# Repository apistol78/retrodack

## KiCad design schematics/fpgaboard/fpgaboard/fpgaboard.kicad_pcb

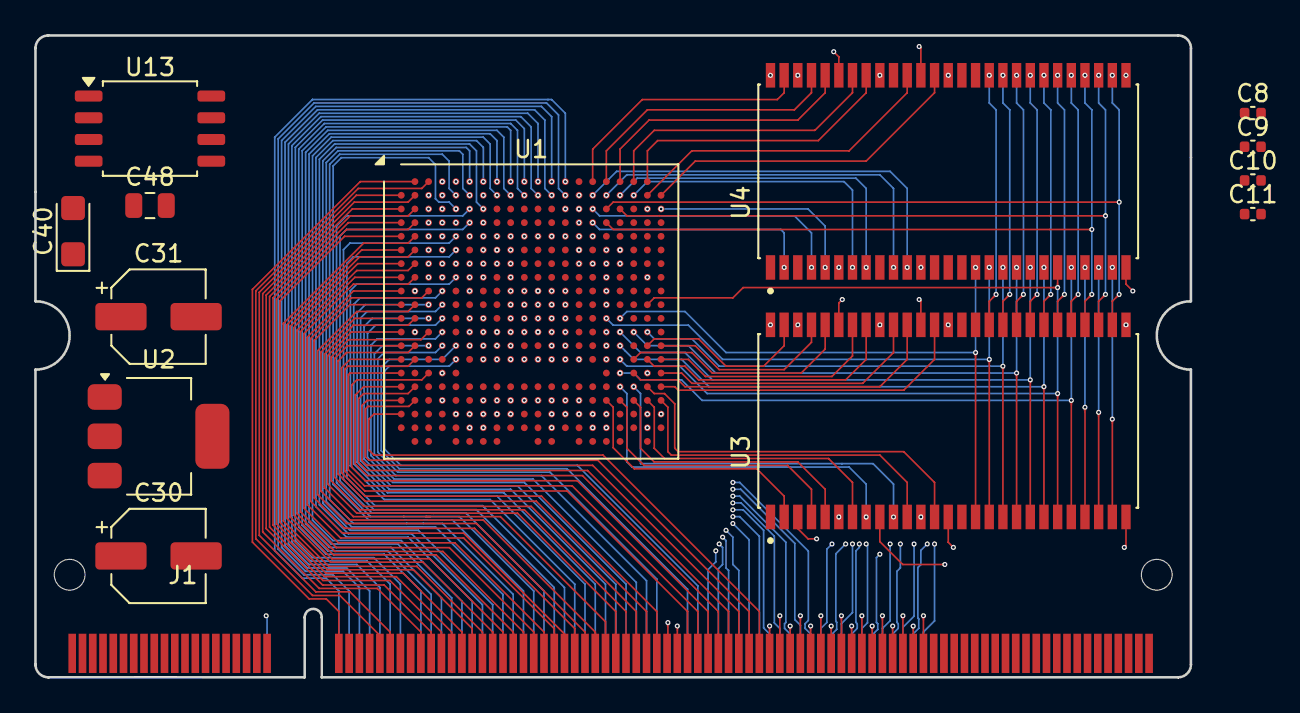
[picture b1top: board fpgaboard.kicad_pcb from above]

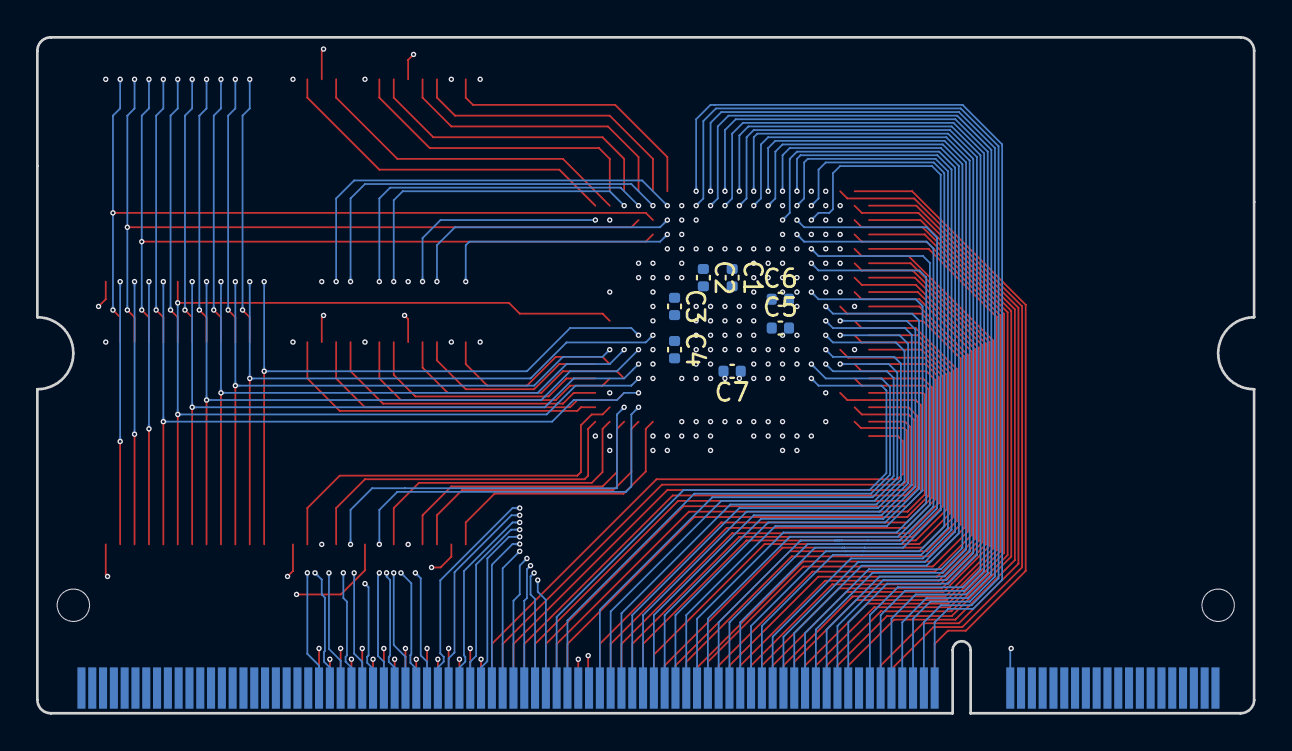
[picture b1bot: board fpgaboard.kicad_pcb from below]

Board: 6 copper layers, 67.6 x 37.5 mm, 21 parts (7 on the bottom side), 171 nets.

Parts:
C1, C2, C3, C4, C5, C6, C7, C8, C9, C10, C11: C_Small; C_0402_1005Metric
C30: 10uF; CP_Elec_5x5.3
C31: 22uF; CP_Elec_5x5.3
C40: 47uF; CP_EIA-3216-18_Kemet-A
C48: 1uF; C_0805_2012Metric
J1: SODIMM-200; SODIMM_DDR2_EDGE
U1: LFE5UM-85F-8BG381I; Lattice_caBGA-381_17x17mm_Layout20x20_P0.8mm
U2: AMS1117-3.3; SOT-223-3_TabPin2
U3, U4: IS42S16320F-7TL; SOP80P1176X120-54N
U13: W25Q32JVSS; SOIC-8_5.3x5.3mm_P1.27mm

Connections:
1v1: U1.H8 (VCC), U1.H9 (VCC), U1.H10 (VCC), U1.H11 (VCC), U1.H12 (VCC), U1.H13 (VCC), U1.J8 (VCC), U1.J13 (VCC), U1.K8 (VCC), U1.K13 (VCC), U1.L8 (VCC), U1.L13 (VCC), U1.M8 (VCC), U1.M13 (VCC), U1.N8 (VCC), U1.N9 (VCC), U1.N10 (VCC), U1.N11 (VCC), U1.N12 (VCC), U1.N13 (VCC)
5V0: C30.1, J1.2, J1.4, J1.6, J1.8, J1.10, J1.12, U2.3 (VI)
FLASH_CLK: U1.U3 (CCLK), U13.6 (CLK)
FLASH_CSn: U1.R2 (PB15A), U13.1 (~CS)
FLASH_IO0: U1.W2 (PB11B), U13.5 (DI/IO_{0})
FLASH_IO1: U1.V2 (PB11A), U13.2 (DO/IO_{1})
FLASH_IO2: U1.Y2 (PB9B), U13.3 (~WP/IO_{2})
FLASH_IO3: U1.W1 (PB9A), U13.7 (~HOLD/~RESET/IO_{3})
GND: C1.2, C2.2, C3.2, C4.2, C5.2, C6.2, C7.2, C8.2, C9.2, C10.2, C11.2, C30.2, C31.2, C40.2, C48.1, J1.1, J1.3, J1.5, J1.7, J1.9, J1.11, J1.39, J1.40, J1.55, J1.56, J1.105, J1.106, J1.107, J1.108, J1.157, J1.158, J1.199, J1.200, U1.B7 (GND), U1.B14 (GND), U1.C19 (GND), U1.D4 (GND), U1.F7 (GND), U1.F8 (GND), U1.F13 (GND), U1.F14 (GND), U1.G4 (GND), U1.G6 (GND), U1.G7 (GND), U1.G8 (GND), U1.G9 (GND), U1.G10 (GND), U1.G11 (GND), U1.G12 (GND), U1.G13 (GND), U1.G14 (GND), U1.G15 (GND), U1.G17 (GND), U1.H19 (GND), U1.J2 (GND), U1.J7 (GND), U1.J9 (GND), U1.J10 (GND), U1.J11 (GND), U1.J12 (GND), U1.J14 (GND), U1.K6 (GND), U1.K7 (GND), U1.K9 (GND), U1.K10 (GND), U1.K11 (GND), U1.K12 (GND), U1.K14 (GND), U1.K15 (GND), U1.L9 (GND), U1.L10 (GND), U1.L11 (GND), U1.L12 (GND), U1.M2 (GND), U1.M7 (GND), U1.M9 (GND), U1.M10 (GND), U1.M11 (GND), U1.M12 (GND), U1.M14 (GND), U1.M16 (GND), U1.N6 (GND), U1.N7 (GND), U1.N14 (GND), U1.N15 (GND), U1.P7 (GND), U1.P8 (GND), U1.P11 (GND), U1.P12 (GND), U1.P13 (GND), U1.P14 (GND), U1.R4 (CFG_2), U1.R19 (GND), U1.U4 (CFG_0), U1.U7 (GND), U1.U8 (GND), U1.U9 (GND), U1.U10 (GND), U1.U11 (GND), U1.U12 (GND), U1.U13 (GND), U1.U14 (GND), U1.V5 (GND), U1.V6 (GND), U1.V7 (GND), U1.V8 (GND), U1.V9 (GND), U1.V12 (GND), U1.V13 (GND), U1.V14 (GND), U1.V15 (GND), U1.V16 (GND), U1.V19 (GND), U1.V20 (GND), U1.W6 (GND), U1.W7 (GND), U1.W12 (GND), U1.W15 (GND), U1.W16 (GND), U1.W19 (GND), U2.1 (GND), U3.6 (VSSQ), U3.12 (VSSQ), U3.28 (VSS), U3.41 (VSS), U3.46 (VSSQ), U3.52 (VSSQ), U3.54 (VSS), U4.6 (VSSQ), U4.12 (VSSQ), U4.28 (VSS), U4.41 (VSS), U4.46 (VSSQ), U4.52 (VSSQ), U4.54 (VSS), U13.4 (GND)
IO_3v3: C1.1, C2.1, C3.1, C4.1, C5.1, C6.1, C7.1, C8.1, C9.1, C10.1, C11.1, C31.1, C40.1, C48.2, U1.F9 (VCCIO0), U1.F10 (VCCIO0), U1.F11 (VCCIO1), U1.F12 (VCCIO1), U1.H6 (VCCIO7), U1.H7 (VCCIO7), U1.H14 (VCCIO2), U1.H15 (VCCIO2), U1.J6 (VCCIO7), U1.J15 (VCCIO2), U1.L6 (VCCIO6), U1.L7 (VCCIO6), U1.L14 (VCCIO3), U1.L15 (VCCIO3), U1.M6 (VCCIO6), U1.M15 (VCCIO3), U1.P9 (VCCIO8), U1.P10 (VCCIO8), U2.2 (VO), U3.1 (VDD), U3.3 (VDDQ), U3.9 (VDDQ), U3.14 (VDD), U3.27 (VDD), U3.43 (VDDQ), U3.49 (VDDQ), U4.1 (VDD), U4.3 (VDDQ), U4.9 (VDDQ), U4.14 (VDD), U4.27 (VDD), U4.43 (VDDQ), U4.49 (VDDQ), U13.8 (VCC)
unnamed: U1.T6 (VCCA0), U1.U6 (VCCA0)
unnamed: U1.T15 (VCCA1), U1.U15 (VCCA1)
unnamed: U1.F6 (VCCAUX), U1.F15 (VCCAUX), U1.P6 (VCCAUX), U1.P15 (VCCAUX)
unnamed: U1.V10 (VCCAUXA0), U1.V11 (VCCAUXA0)
unnamed: U1.V17 (VCCAUXA1), U1.V18 (VCCAUXA1)
RAM_A0: U1.R17 (PR56D), U3.23 (A0), U4.23 (A0)
RAM_A1: U1.E20 (PR38A), U3.24 (A1), U4.24 (A1)
RAM_A2: U1.F19 (PR38B), U3.25 (A2), U4.25 (A2)
RAM_A3: U1.F20 (PR38C), U3.26 (A3), U4.26 (A3)
RAM_A4: U1.C16 (PT112A), U1.G20 (PR38D), U3.29 (A4), U4.29 (A4)
RAM_A5: U1.C17 (PT114B), U1.G19 (PR41A), U3.30 (A5), U4.30 (A5)
RAM_A6: U1.D16 (PT112B), U1.H20 (PR41B), U3.31 (A6), U4.31 (A6)
RAM_A7: U1.J18 (PR41C), U3.32 (A7), U4.32 (A7)
RAM_A8: U1.K18 (PR41D), U3.33 (A8), U4.33 (A8)
RAM_A9: U1.J19 (PR44A), U3.34 (A9), U4.34 (A9)
RAM_A10: U1.P17 (PR53D), U3.22 (A10), U4.22 (A10)
RAM_A11: U1.J20 (PR44C), U3.35 (A11), U4.35 (A11)
RAM_A12: U1.K20 (PR44D), U3.36 (A12), U4.36 (A12)
RAM_BA0: U1.M17 (PR53B), U3.20 (BA0), U4.20 (BA0)
RAM_BA1: U1.N17 (PR56A), U3.21 (BA1), U4.21 (BA1)
RAM_CKE: U1.M20 (PR47B), U3.37 (CKE), U4.37 (CKE)
RAM_CLK: U1.L20 (PR47A), U3.38 (CLK), U4.38 (CLK)
RAM_D0: U1.U16 (PR92C), U3.2 (DQ0)
RAM_D1: U1.U17 (PR92B), U3.4 (DQ1)
RAM_D2: U1.U18 (PR92A), U3.5 (DQ2)
RAM_D3: U1.U19 (PR89C), U3.7 (DQ3)
RAM_D4: U1.T17 (PR92D), U3.8 (DQ4)
RAM_D5: U1.T18 (PR89D), U3.10 (DQ5)
RAM_D6: U1.U20 (PR86D), U3.11 (DQ6)
RAM_D7: U1.T19 (PR89A), U3.13 (DQ7)
RAM_D8: U1.T20 (PR86C), U3.42 (DQ8)
RAM_D9: U1.R18 (PR89B), U3.44 (DQ9)
RAM_D10: U1.R20 (PR86B), U3.45 (DQ10)
RAM_D11: U1.P19 (PR83C), U3.47 (DQ11)
RAM_D12: U1.P20 (PR86A), U3.48 (DQ12)
RAM_D13: U1.P18 (PR83D), U3.50 (DQ13)
RAM_D14: U1.N20 (PR83B), U3.51 (DQ14)
RAM_D15: U1.N19 (PR83A), U3.53 (DQ15)
RAM_D16: U1.D15 (PT107A), U4.2 (DQ0)
RAM_D17: U1.C15 (PT105B), U4.4 (DQ1)
RAM_D18: U1.C20 (PR35A), U4.5 (DQ2)
RAM_D19: U1.B18 (PT116B), U4.7 (DQ3)
RAM_D20: U1.B17 (PT114A), U4.8 (DQ4)
RAM_D21: U1.B16 (PT110B), U4.10 (DQ5)
RAM_D22: U1.B15 (PT105A), U4.11 (DQ6)
RAM_D24: U1.B20 (PT121B), U4.42 (DQ8)
RAM_D27: U1.A19 (PT121A), U4.47 (DQ11)
RAM_D28: U1.A18 (PT119A), U4.48 (DQ12)
RAM_D29: U1.A17 (PT116A), U4.50 (DQ13)
RAM_D30: U1.A16 (PT110A), U4.51 (DQ14)
RAM_D31: U1.A15 (PT103A), U4.53 (DQ15)
S1: J1.41, U1.A2 (PL35A)
S2: J1.49, U1.A3 (PL14C)
S3: J1.51, U1.B1 (PL35B)
S4: J1.57, U1.B2 (PL35C)
S5: J1.59, U1.C1 (PL38A)
S6: J1.61, U1.C2 (PL35D)
S7: J1.63, U1.D1 (PL38B)
S8: J1.65, U1.D2 (PL38C)
S9: J1.67, U1.E1 (PL38D)
S10: J1.69, U1.E2 (PL44D)
S11: J1.71, U1.F1 (PL47B)
S12: J1.73, U1.F2 (PL44C)
S13: J1.75, U1.G1 (PL47D)
S14: J1.77, U1.G2 (PL47A)
S15: J1.79, U1.H1 (PL53C)
S16: J1.81, U1.H2 (PL47C)
S17: J1.83, U1.J1 (PL53B)
S18: J1.85, U1.J3 (PL50C)
S19: J1.87, U1.K1 (PL53D)
S20: J1.89, U1.K2 (PL53A)
S21: J1.91, U1.L1 (PL89C)
S22: J1.93, U1.L2 (PL86D)
S23: J1.95, U1.M1 (PL89B)
S24: J1.97, U1.M3 (PL86B)
S25: J1.99, U1.N1 (PL89D)
S26: J1.101, U1.N2 (PL89A)
S27: J1.103, U1.P1 (PL92A)
S28: J1.109, U1.P2 (PL92B)
S29: J1.111, U1.R1 (PB4A)
S30: J1.113, U1.R3 (PB15B)
S31: J1.115, U1.T1 (PB4B)
S32: J1.117, U1.T2 (PB13A)
S33: J1.119, U1.U1 (PB6A)
S34: J1.121, U1.U2 (PB13B)
S35: J1.123, U1.V1 (PB6B)
S36: J1.125, U1.A4 (PL11A)
S37: J1.127, U1.A5 (PL11B)
S38: J1.129, U1.B3 (PL14D)
S39: J1.131, U1.B4 (PL14B)
S40: J1.133, U1.C3 (PL17C)
S41: J1.135, U1.C4 (PL14A)
S42: J1.137, U1.D3 (PL17D)
S43: J1.139, U1.D5 (PL17B)
S44: J1.141, U1.E3 (PL20B)
S45: J1.143, U1.E4 (PL17A)
S46: J1.145, U1.F3 (PL44B)
S47: J1.147, U1.F4 (PL20A)
S48: J1.149, U1.G3 (PL44A)
S49: J1.151, U1.G5 (PL41B)
S50: J1.153, U1.H3 (PL41D)
S51: J1.155, U1.H4 (PL41A)
S52: J1.42, U1.A13 (PT76B)
S53: J1.44, U1.B13 (PT78A)
S54: J1.46, U1.A12 (PT76A)
S55: J1.48, U1.B12 (PT71A)
S56: J1.50, U1.A11 (PT63B)
S57: J1.52, U1.B11 (PT65A)
S58: J1.54, U1.A10 (PT63A)
S59: J1.58, U1.B10 (PT60B)
S60: J1.60, U1.A9 (PT60A)
S61: J1.62, U1.B9 (PT58A)
S62: J1.64, U1.A8 (PT18B)
S63: J1.66, U1.B8 (PT15B)
S64: J1.68, U1.A7 (PT18A)
S65: J1.70, U1.C7 (PT11B)
S66: J1.72, U1.A6 (PT4A)
S67: J1.74, U1.B6 (PT4B)
S68: J1.76, U1.B5 (PL11C)
S69: J1.78, U1.C5 (PL11D)
S70: J1.80, U1.C6 (PT11A)
S71: J1.82, U1.D6 (PT6B)
S72: J1.84, U1.E5 (PL20C)
S73: J1.86, U1.F5 (PL20D)
S74: J1.88, U1.H5 (PL41C)
S75: J1.90, U1.J4 (PL50A)
S76: J1.92, U1.K3 (PL50D)
S77: J1.94, U1.K4 (PL56A)
S78: J1.96, U1.L3 (PL86C)
S79: J1.98, U1.L4 (PL56C)
S80: J1.100, U1.M4 (PL83A)
S81: J1.102, U1.N3 (PL86A)
S82: J1.104, U1.N4 (PL83C)
S83: J1.110, U1.N5 (PL83B)
S84: J1.112, U1.P5 (PL83D)
S85: J1.114, U1.E6 (PT6A)
S86: J1.116, U1.D7 (PT9B)
S87: J1.118, U1.E7 (PT9A)
S88: J1.120, U1.E8 (PT13A)
S89: J1.122, U1.E9 (PT20B)
S90: J1.124, U1.E10 (PT56B)
S91: J1.126, U1.E11 (PT69B)
S92: J1.128, U1.E12 (PT74B)
S93: J1.130, U1.E13 (PT80B)
S94: J1.132, U1.E14 (PT85B)
S95: J1.134, U1.F16 (PR11D)
S96: J1.136, U1.P16 (PR56B)
S97: J1.138, U1.N16 (PR53A)
S98: J1.140, U1.K16 (PR29A)
S99: J1.142, U1.J16 (PR20D)
S100: J1.144, U1.H16 (PR17D)
S101: J1.146, U1.G16 (PR17C)
S102: J1.148, U1.F17 (PR17A)
S103: J1.150, U1.E15 (PT107B)
S104: J1.152, U1.D14 (PT85A)
S105: J1.154, U1.C13 (PT78B)
S106: J1.156, U1.C14 (PT83B)
~RAM_CAS: U1.L16 (PR50A), U3.17 (~CAS), U4.17 (~CAS)
~RAM_CS: U1.M18 (PR50D), U3.19 (~CS), U4.19 (~CS)
~RAM_RAS: U1.M19 (PR47D), U3.18 (~RAS), U4.18 (~RAS)
~RAM_WE: U1.L17 (PR50B), U3.16 (~WE), U4.16 (~WE)

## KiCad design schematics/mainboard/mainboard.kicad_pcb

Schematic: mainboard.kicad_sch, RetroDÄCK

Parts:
C1, C17, C27, C30: 10uF; CP_Elec_5x5.3
C2, C31: 22uF; CP_Elec_5x5.3
C3, C4, C5, C6, C7, C8, C10, C11, C12, C13, C14, C48, C49: 1uF; C_0805_2012Metric
C9: 4.7uF; C_0805_2012Metric
C15, C21, C23, C26, C32, C35, C36: 0.1uF; C_0805_2012Metric_Pad1.18x1.45mm_HandSolder; LCSC C28233
C16, C28, C29: 10uF; C_0805_2012Metric
C18: 0.1uF; C_0805_2012Metric
C19, C20: 27pF; C_0805_2012Metric
C22, C24, C33, C37: 10uF; C_0805_2012Metric_Pad1.18x1.45mm_HandSolder; LCSC C1713
C25, C40, C43, C45: 47uF; CP_EIA-3216-18_Kemet-A; LCSC C7190
C34, C38: 22uF; C_0805_2012Metric_Pad1.18x1.45mm_HandSolder; LCSC C15850
C39: 47uF; CP_Elec_5x5.3
C41: 500pF; C_0805_2012Metric
C42: 10uF; CP_EIA-3216-18_Kemet-A; LCSC C1969735
C44: 0.47uF; C_0805_2012Metric_Pad1.18x1.45mm_HandSolder
C46, C47: 47uF; C_0805_2012Metric_Pad1.18x1.45mm_HandSolder
D1, D3: LED; LED_0805_2012Metric; LCSC C2297
H1, H2, H3, H4, H5, H6, H7, H8: MountingHole; MountingHole_2.5mm
J1: SD_Card_Receptacle; RetroDACK SD_Hirose_DM1AA_SF_PEJ82; LCSC C506790
J2: LCD_CONN; PinHeader_2x20_P2.54mm_Vertical
J3: USB_C_Receptacle_USB2.0_16P; USB_C_Receptacle_GCT_USB4105-xx-A_16P_TopMnt_Horizontal
J4: BATTERY_CONN; JST_PH_S2B-PH-K_1x02_P2.00mm_Horizontal
J5: 527461671; CON_527461671_MOL; LCSC C3169781
J6: SPEAKER_CONN; JST_PH_S2B-PH-K_1x02_P2.00mm_Horizontal
J7: Conn_01x06; PinHeader_1x06_P2.54mm_Vertical
L1: 2.2uH; L_APV_ANR4012; LCSC C36409
P1: 1-1473005-4; TE_1-1473005-4; LCSC C428482
R1, R2: 33; R_0603_1608Metric_Pad0.98x0.95mm_HandSolder
R3, R4: 1.2k; R_0603_1608Metric_Pad0.98x0.95mm_HandSolder
R5: 100; R_0603_1608Metric
R6, R7: 5.1k; R_0603_1608Metric_Pad0.98x0.95mm_HandSolder
R8, R9, R10, R11, R12, R13, R14, R15, R16, R18, R19, R20, R28, R31, R35, R36: 10k; R_0603_1608Metric_Pad0.98x0.95mm_HandSolder
R17, R33, R34: 4k7; R_0603_1608Metric_Pad0.98x0.95mm_HandSolder; LCSC C17673
R21, R22, R23, R24, R25: 4k7; R_0603_1608Metric_Pad0.98x0.95mm_HandSolder
R26: 120; R_0603_1608Metric_Pad0.98x0.95mm_HandSolder
R27: 68; R_0603_1608Metric_Pad0.98x0.95mm_HandSolder
R29: 0; R_0805_2012Metric_Pad1.20x1.40mm_HandSolder
R30: 10m (1%, 1W); R_0805_2012Metric
R32: NC; R_0603_1608Metric_Pad0.98x0.95mm_HandSolder
S1: SSSS811101; SW_SSSS811101; PARTREV N/A
U1, U2: AMS1117-3.3; SOT-223-3_TabPin2
U3: MAX3421EETJ_T; QFP50P700X700X120-32N; LCSC C2651881
U4: SOP80P1176X120-54N; LCSC C2959389
U5: AMS1117-1.8; SOT-223-3_TabPin2; LCSC C6185
U6: TPS63002; Texas_DRC0010J_ThermalVias; LCSC C116655
U7: BQ24072RGT; VQFN-16-1EP_3x3mm_P0.5mm_EP1.6x1.6mm; LCSC C81080
U8: QFN50P500X500X100-33N; LCSC C2667049
U9: TPS22917DBV; SOT-23-6; LCSC C2681320
U10: PCA9555PW; TSSOP-24_4.4x7.8mm_P0.65mm; LCSC C128392
U11: PJ-327E-5A; LCSC C145812
U13: W25Q32JVSS; SOIC-8_5.3x5.3mm_P1.27mm; LCSC C82344
U14: DS3231MZ; SOIC-8_3.9x4.9mm_P1.27mm; LCSC C107410
U15: BQ27441DRZT-G1A; Texas_S-PDSO-N12; LCSC C2864880
Y1: 12MHz; Crystal_SMD_HC49-SD

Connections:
1V8: C21.1, C22.1, C25.1, U5.2 (VO), U8.3 (DVDD)
3V3: C6.1, C7.1, C8.2, C10.2, C11.2, C12.2, C13.2, C14.2, C23.1, C24.1, C26.1, C31.1, C33.1, C35.1, C37.1, C40.1, C42.1, C49.2, J5.15, R8.2, R9.2, R10.2, R11.2, R12.2, R13.2, R14.2, R15.2, R16.2, R17.1, R18.2, R20.2, R33.1, R34.1, R36.2, U2.2 (VO), U3.2 (VL), U3.23 (VCC), U4.2 (VCC), U4.14 (VCC), U4.16 (~CE2), U4.23 (VCC), U4.29 (VCC), U4.50 (VCC), U5.3 (VI), U8.2 (IOVDD), U8.17 (AVDD), U8.28 (HPVDD), U10.24 (VDD), U14.2 (VCC)
3V3_LCD: C2.1, C3.2, C4.2, C39.1, C43.1, C48.2, J1.4 (VDD), J1.14 (CARD_DETECT), J2.1, J2.17, R21.2, R22.2, R23.2, R24.2, R25.2, U1.2 (VO), U13.8 (VCC)
5V0: C1.1, C16.2, C29.2, C30.1, C32.1, C34.1, C36.1, C38.1, C45.1, J2.2, J2.4, P1.2, P1.4, P1.6, P1.8, P1.10, P1.12, U1.3 (VI), U2.3 (VI), U6.1 (VOUT), U6.10 (FB), U8.21 (SPKVDD), U8.24 (SPKVDD)
AUDIO_BCLK: P1.66, U8.7 (BCLK)
AUDIO_DIN: P1.70, U8.5 (DIN)
AUDIO_INTERRUPT: P1.72, U8.32 (GPIO1)
AUDIO_MCLK: P1.64, U8.8 (MCLK)
AUDIO_WCLK: P1.68, U8.6 (WCLK)
BAT+: J4.1, R30.2, U15.6 (BAT), U15.8 (SRP)
BAT_SYS+: C9.2, R30.1, U7.2 (BAT), U7.3 (BAT), U14.6 (VBAT), U15.7 (SRN)
FLASH_CLK: P1.92, U13.6 (CLK)
FLASH_CSn: P1.84, U13.1 (~CS)
FLASH_IO0: P1.90, U13.5 (DI/IO_{0})
FLASH_IO1: P1.86, U13.2 (DO/IO_{1})
FLASH_IO2: P1.88, U13.3 (~WP/IO_{2})
FLASH_IO3: P1.94, U13.7 (~HOLD/~RESET/IO_{3})
GND: C1.2, C2.2, C3.1, C4.1, C5.1, C6.2, C7.2, C8.1, C9.1, C10.1, C11.1, C12.1, C13.1, C14.1, C15.2, C16.1, C17.2, C18.1, C19.1, C20.1, C21.2, C22.2, C23.2, C24.2, C25.2, C26.2, C27.2, C28.1, C29.1, C30.2, C31.2, C32.2, C33.2, C34.2, C35.2, C36.2, C37.2, C38.2, C39.2, C40.2, C42.2, C43.2, C44.2, C45.2, C48.1, C49.1, J1.3 (VSS), J1.6 (VSS), J1.12 (SHELL1), J1.13 (SHELL2), J2.6, J2.9, J2.14, J2.20, J2.25, J2.30, J2.34, J2.39, J3.A1 (GND), J3.A12 (GND), J3.B1 (GND), J3.B12 (GND), J3.S1 (SHIELD), J4.2, J5.1, J5.P1, J5.P2, J7.1, P1.1, P1.3, P1.5, P1.7, P1.9, P1.11, P1.39, P1.40, P1.55, P1.56, P1.105, P1.106, P1.107, P1.108, P1.157, P1.158, P1.199, P1.200, R3.2, R4.2, R6.1, R7.1, R19.2, R28.2, R35.2, U1.1 (GND), U2.1 (GND), U3.3 (GND), U3.19 (GND), U4.5 (VSS), U4.13 (~CE1), U4.26 (VSS), U4.32 (VSS), U4.41 (VSS), U4.53 (VSS), U5.1 (GND), U6.3 (PGND), U6.9 (GND), U6.11 (PGND), U7.4 (~CE), U7.6 (EN1), U7.8 (VSS), U7.17 (VSS), U8.1 (IOVSS), U8.13 (AIN1), U8.14 (AIN2), U8.16 (AVSS), U8.18 (DVSS), U8.20 (SPKVSS), U8.25 (SPKVSS), U8.29 (HPVSS), U9.2 (GND), U10.2 (A1), U10.3 (A2), U10.12 (VSS), U10.21 (A0), U11.1 (GND), U13.4 (GND), U14.5 (GND), U15.3 (V_{SS})
I2C_SCL: J5.13, P1.60, R34.2, U8.10 (SCL), U10.22 (SCL), U14.8 (SCL), U15.2 (SCL)
I2C_SDA: J5.12, P1.58, R33.2, U8.9 (SDA), U10.23 (SDA), U14.7 (SDA), U15.1 (SDA)
KEYPAD_INTERRUPT: P1.155, R18.1, U10.1 (~INT)
LCD_B0: J2.7, P1.114
LCD_B1: J2.29, P1.142
LCD_B2: J2.31, P1.144
LCD_B3: J2.26, P1.136
LCD_B4: J2.24, P1.134
LCD_B5: J2.21, P1.132
LCD_BACKLIGHT_CTRL: J2.35, P1.152
LCD_CLK: J2.27, P1.138
LCD_CS: J2.12, P1.122
LCD_ENABLE: J2.28, P1.140
LCD_G0: J2.32, P1.146
LCD_G1: J2.33, P1.148
LCD_G2: J2.8, P1.116
LCD_G3: J2.10, P1.118
LCD_G4: J2.36, P1.150
LCD_G5: J2.11, P1.120
LCD_HSYNC: J2.5, P1.112
LCD_R0: J2.38, P1.154
LCD_R1: J2.40, P1.156
LCD_R2: J2.15, P1.126
LCD_R3: J2.16, P1.124
LCD_R4: J2.18, P1.128
LCD_R5: J2.22, P1.130
LCD_VSYNC: J2.3, P1.110
unnamed: D1.2 (A), R27.2
unnamed: D1.1 (K), U7.9 (~CHG)
unnamed: D3.2 (A), R26.2
unnamed: D3.1 (K), U7.7 (~PGOOD)
unnamed: J3.A5 (CC1), R7.2
unnamed: J3.B5 (CC2), R6.2
unnamed: J6.1, U8.22 (SPKP), U8.26 (SPKP)
unnamed: J6.2, U8.19 (SPKM), U8.23 (SPKM)
unnamed: J7.2, P1.82
unnamed: J7.3, P1.80
unnamed: J7.4, P1.78
unnamed: J7.5, P1.76
unnamed: J7.6, P1.74
unnamed: R1.2, U3.21 (D+)
unnamed: R2.2, U3.20 (D-)
unnamed: C5.2, R29.1, U3.22 (VBCOMP)
unnamed: C18.2, R5.1, U6.6 (EN), U6.7 (PS/SYNC), U6.8 (VINA)
unnamed: L1.2, U6.4 (L1)
unnamed: L1.1, U6.2 (L2)
unnamed: C28.2, C41.1, R26.1, R27.1, S1.2, U7.5 (EN2), U7.10 (OUT), U7.11 (OUT), U7.15 (TD), U9.1 (VIN)
unnamed: R3.1, U7.12 (ILIM)
unnamed: R4.1, U7.16 (ISET)
unnamed: R28.1, U7.1 (TS)
unnamed: C47.1, U8.27 (HPL)
unnamed: C46.1, U8.30 (HPR)
unnamed: R31.1, U8.12 (MICBIAS)
unnamed: C41.2, U9.4 (CT)
unnamed: R19.1, S1.1, U9.3 (ON)
unnamed: R32.2, U9.5 (QOD)
unnamed: J5.2, R8.1, U10.4 (IO0_0)
unnamed: J5.3, R12.1, U10.5 (IO0_1)
unnamed: J5.4, R9.1, U10.6 (IO0_2)
unnamed: J5.5, R13.1, U10.7 (IO0_3)
unnamed: J5.6, R10.1, U10.8 (IO0_4)
unnamed: J5.7, R14.1, U10.9 (IO0_5)
unnamed: J5.8, R11.1, U10.10 (IO0_6)
unnamed: J5.9, R15.1, U10.11 (IO0_7)
unnamed: J5.10, R16.1, U10.13 (IO1_0)
unnamed: J5.11, R20.1, U10.14 (IO1_1)
unnamed: R31.2, U8.11 (VOL/MICDET), U11.4 (DETECT_GND)
unnamed: C47.2, U11.2 (LEFT)
unnamed: C46.2, U11.3 (RIGHT)
unnamed: R35.1, U15.10 (BIN)
unnamed: R36.1, U15.12 (GPOUT)
unnamed: C44.1, U15.5 (V_{DD})
SD_CARD: J1.10 (CARD_DETECT), P1.54
SD_CLK: J1.5 (CLK), P1.46
SD_CMD: J1.2 (CMD), P1.48, R25.1
SD_DAT0: J1.7 (DAT0), P1.44, R21.1
SD_DAT1: J1.8 (DAT1), P1.42, R22.1
SD_DAT2: J1.9 (DAT2), P1.52, R23.1
SD_DAT3: J1.1 (CD/DAT3), P1.50, R24.1
SRAM_A0: P1.119, U4.11 (A0)
SRAM_A1: P1.123, U4.10 (A1)
SRAM_A2: P1.127, U4.9 (A2)
SRAM_A3: P1.131, U4.8 (A3)
SRAM_A4: P1.135, U4.7 (A4)
SRAM_A5: P1.133, U4.48 (A5)
SRAM_A6: P1.129, U4.47 (A6)
SRAM_A7: P1.125, U4.46 (A7)
SRAM_A8: P1.121, U4.45 (A8)
SRAM_A9: P1.117, U4.44 (A9)
SRAM_A10: P1.103, U4.38 (A10)
SRAM_A11: P1.99, U4.37 (A11)
SRAM_A12: P1.95, U4.36 (A12)
SRAM_A13: P1.91, U4.35 (A13)
SRAM_A14: P1.87, U4.34 (A14)
SRAM_A15: P1.85, U4.21 (A15)
SRAM_A16: P1.89, U4.20 (A16)
SRAM_A17: P1.93, U4.19 (A17)
SRAM_A18: P1.97, U4.18 (A18)
SRAM_A19: P1.101, U4.17 (A19)
SRAM_D0: P1.81, U4.22 (IO_0)
SRAM_D1: P1.77, U4.24 (IO_1)
SRAM_D2: P1.73, U4.25 (IO_2)
SRAM_D3: P1.69, U4.27 (IO_3)
SRAM_D4: P1.71, U4.28 (IO_4)
SRAM_D5: P1.75, U4.30 (IO_5)
SRAM_D6: P1.79, U4.31 (IO_6)
SRAM_D7: P1.83, U4.33 (IO_7)
SRAM_D8: P1.137, U4.49 (IO_8)
SRAM_D9: P1.141, U4.51 (IO_9)
SRAM_D10: P1.145, U4.52 (IO_10)
SRAM_D11: P1.149, U4.54 (IO_11)
SRAM_D12: P1.151, U4.1 (IO_12)
SRAM_D13: P1.147, U4.3 (IO_13)
SRAM_D14: P1.143, U4.4 (IO_14)
SRAM_D15: P1.139, U4.6 (IO_15)
SYS_LOAD: C17.1, R5.2, R32.1, U6.5 (VIN), U9.6 (VOUT)
TRACKBALL_INTERRUPT: J5.14, P1.62
USB_DN: J3.A7 (D-), J3.B7 (D-), R2.1
USB_DP: J3.A6 (D+), J3.B6 (D+), R1.1
USB_HCI_INT: P1.57, U3.18 (INT)
USB_HCI_MISO: P1.61, U3.15 (MISO)
USB_HCI_MOSI: P1.59, U3.16 (MOSI)
USB_HCI_SCLK: P1.65, U3.13 (SCLK)
USB_HCI_XI: C19.2, U3.24 (XI), Y1.1
USB_HCI_XO: C20.2, U3.25 (XO), Y1.2
USB_VBUS: C27.1, J3.A4 (VBUS), J3.A9 (VBUS), J3.B4 (VBUS), J3.B9 (VBUS), R29.2, U7.13 (IN)
~RESET: C15.1, R17.2, U8.31 (~RESET)
~SRAM_BHE: P1.115, U4.12 (~BHE)
~SRAM_BLE: P1.109, U4.39 (~BLE)
~SRAM_OE: P1.113, U4.42 (~OE)
~SRAM_WE: P1.111, U4.15 (~WE)
~USB_HCI_RESET: P1.67, U3.12 (~RES)
~USB_HCI_SS: P1.63, U3.14 (~SS)

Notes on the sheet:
SRAM
SD CARD
BATTERY MNGR
TLV320 I2C address 0x18
CE2 if U4 is NOT inverted! Symbol incorrect!
I2C address 0x55 (7-bit)
Trackball I2C address 0x0A
REGULATORS
I2C address 0xD0
AUDIO
I2C address 0x40
NV STORAGE
Switch current min 1600 mA
INPUT CONNECTORS
USB INTERFACE
LCD CONNECTOR
RTC
Battery terminal JST-PH
TODO -GPIO with debounce? +Battery ADC -Charge signal to FPGA (open drain?) -What if battery/USB are connected at the same time as "ice" USB? -Power switch, larger? +Headphone detection, MIC/VOLDET need to be pulled down from a R to MIC +Headphone caps on +/- +Improved bulk and filter of 5V

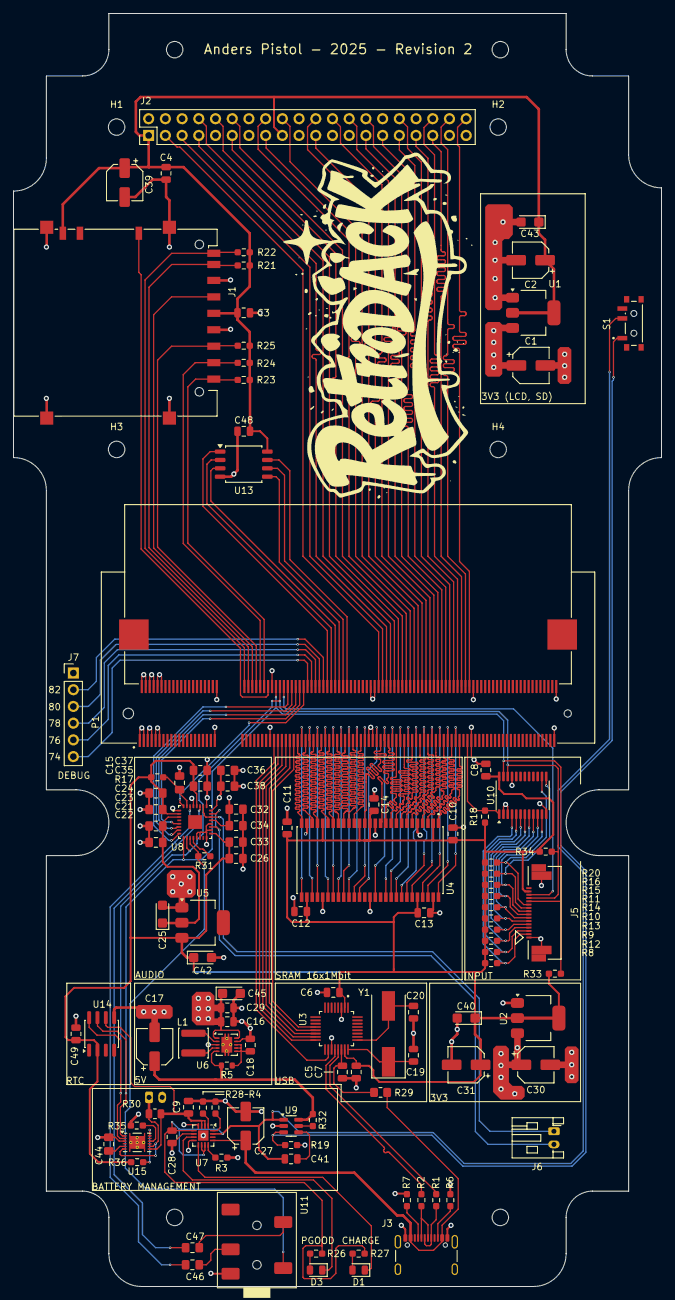
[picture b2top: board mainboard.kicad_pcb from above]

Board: 4 copper layers, 98.5 x 193.5 mm, 120 parts (1 on the bottom side), 151 nets.

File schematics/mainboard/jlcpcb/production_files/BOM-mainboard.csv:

Comment,Designator,Footprint,LCSC,Quantity
0,R29,R_0805_2012Metric_Pad1.20x1.40mm_HandSolder,C17477,1
0.1uF,"C15,C18,C21,C23,C26,C32,C35,C36",C_0805_2012Metric_Pad1.18x1.45mm_HandSolder,C49678,8
0.47uF,C44,C_0805_2012Metric_Pad1.18x1.45mm_HandSolder,C28233,1
1-1473005-4,P1,TE_1-1473005-4,C428482,1
1.2k,"R3,R4",R_0603_1608Metric_Pad0.98x0.95mm_HandSolder,C22765,2
100,R5,R_0603_1608Metric,C22775,1
10k,"R10,R11,R12,R13,R14,R15,R16,R18,R19,R20,R28,R31,R35,R36,R8,R9",R_0603_1608Metric_Pad0.98x0.95mm_HandSolder,C25804,16
"10m (1%, 1W)",R30,R_0805_2012Metric,C728271,1
10uF,"C16,C22,C24,C28,C29,C33,C37",C_0805_2012Metric,C15850,7
10uF,"C1,C17,C27,C30",CP_Elec_5x5.3,C249823,4
10uF,C42,CP_EIA-3216-18_Kemet-A,C74423,1
120,R26,R_0603_1608Metric_Pad0.98x0.95mm_HandSolder,C22787,1
12MHz,Y1,Crystal_SMD_HC49-SD,C521722,1
1uF,"C10,C11,C12,C13,C14,C3,C4,C48,C49,C5,C6,C7,C8",C_0805_2012Metric,C28323,13
2.2uH,L1,L_APV_ANR4012,C36409,1
22uF,"C2,C31",CP_Elec_5x5.3,C249605,2
22uF,"C34,C38",C_0805_2012Metric_Pad1.18x1.45mm_HandSolder,C45783,2
27pF,"C19,C20",C_0805_2012Metric,C1804,2
33,"R1,R2",R_0603_1608Metric_Pad0.98x0.95mm_HandSolder,C23140,2
4.7uF,C9,C_0805_2012Metric,C1779,1
47uF,"C25,C40,C43,C45",CP_EIA-3216-18_Kemet-A,C131173,4
47uF,"C46,C47",C_0805_2012Metric_Pad1.18x1.45mm_HandSolder,C16780,2
47uF,C39,CP_Elec_5x5.3,C249532,1
4k7,"R17,R21,R22,R23,R24,R25,R33,R34",R_0603_1608Metric_Pad0.98x0.95mm_HandSolder,C23162,8
5.1k,"R6,R7",R_0603_1608Metric_Pad0.98x0.95mm_HandSolder,C23186,2
500pF,C41,C_0805_2012Metric,C1743,1
527461671,J5,CON_527461671_MOL,C3169781,1
68,R27,R_0603_1608Metric_Pad0.98x0.95mm_HandSolder,C22775,1
AMS1117-1.8,U5,SOT-223-3_TabPin2,C6185,1
AMS1117-3.3,"U1,U2",SOT-223-3_TabPin2,C6186,2
BQ24072RGT,U7,VQFN-16-1EP_3x3mm_P0.5mm_EP1.6x1.6mm,C140288,1
BQ27441DRZT-G1A,U15,Texas_S-PDSO-N12,C2864880,1
DS3231MZ,U14,SOIC-8_3.9x4.9mm_P1.27mm,C107410,1
LED,D3,LED_0805_2012Metric,C2297,1
LED,D1,LED_0805_2012Metric,C34499,1
MAX3421EETJ_T,U3,QFP50P700X700X120-32N,C2651881,1
PCA9555PW,U10,TSSOP-24_4.4x7.8mm_P0.65mm,C128392,1
SD_Card_Receptacle,J1,RetroDACK SD_Hirose_DM1AA_SF_PEJ82,C506790,1
SSSS811101,S1,SW_SSSS811101,C109335,1
TPS22917DBV,U9,SOT-23-6,C2681320,1
TPS63002,U6,Texas_DRC0010J_ThermalVias,C116655,1
USB_C_Receptacle_USB2.0_16P,J3,USB_C_Receptacle_GCT_USB4105-xx-A_16P_TopMnt_Horizontal,C3020560,1
W25Q32JVSS,U13,SOIC-8_5.3x5.3mm_P1.27mm,C82344,1
~,U11,PJ-327E-5A,C145812,1
~,U8,QFN50P500X500X100-33N,C2667049,1
~,U4,SOP80P1176X120-54N,C2959389,1
LCD_CONN,J2,PinHeader_2x20_P2.54mm_Vertical,,1
BATTERY_CONN,J4,JST_PH_S2B-PH-K_1x02_P2.00mm_Horizontal,,1
SPEAKER_CONN,J6,JST_PH_S2B-PH-K_1x02_P2.00mm_Horizontal,,1
NC,R32,R_0603_1608Metric_Pad0.98x0.95mm_HandSolder,,1
Conn_01x06,J7,PinHeader_1x06_P2.54mm_Vertical,,1

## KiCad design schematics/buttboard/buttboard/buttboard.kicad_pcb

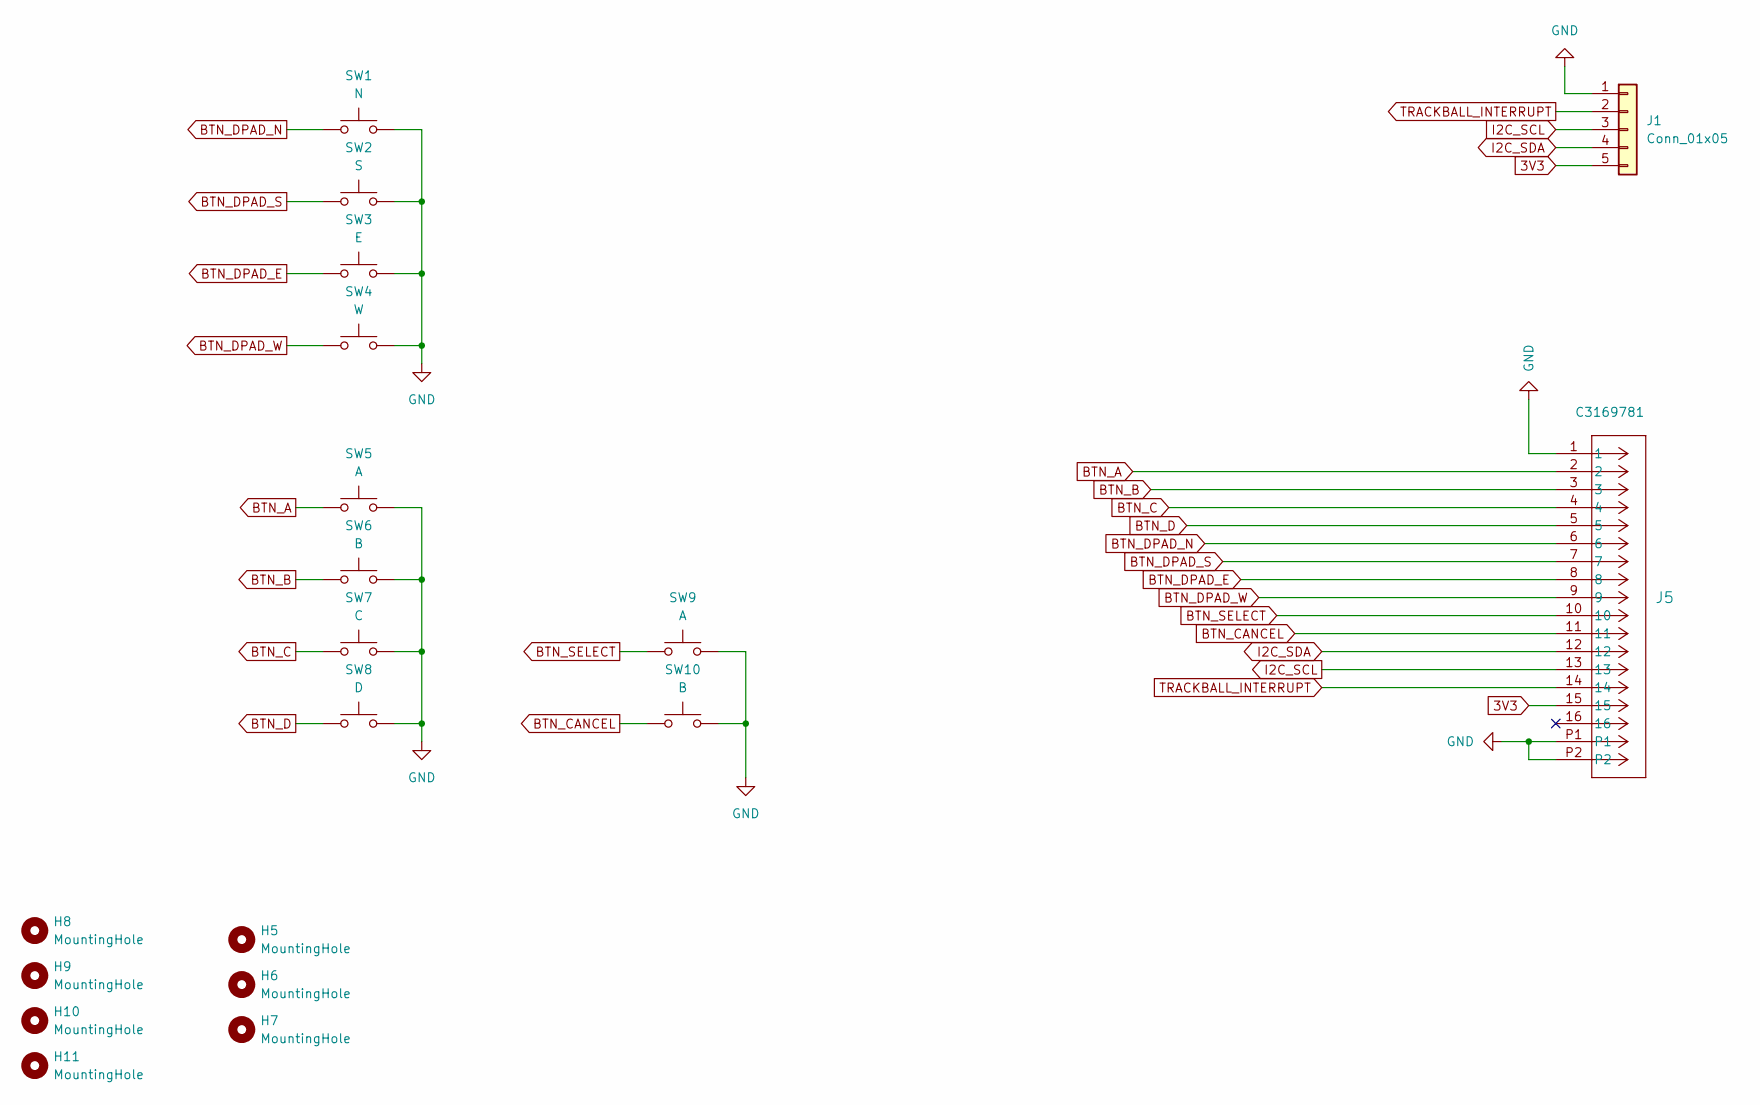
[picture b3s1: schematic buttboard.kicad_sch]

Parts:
H5, H6, H7, H8, H9, H10, H11: MountingHole; MountingHole_3mm
J1: Conn_01x05; PinHeader_1x05_P2.54mm_Vertical
J5: 527461671; CON_527461671_MOL; LCSC C3169781
SW1: N; SW_PUSH_6mm_H7.3mm
SW2: S; SW_PUSH_6mm_H7.3mm
SW3: E; SW_PUSH_6mm_H7.3mm
SW4: W; SW_PUSH_6mm_H7.3mm
SW5, SW9: A; SW_PUSH_6mm_H7.3mm
SW6, SW10: B; SW_PUSH_6mm_H7.3mm
SW7: C; SW_PUSH_6mm_H7.3mm
SW8: D; SW_PUSH_6mm_H7.3mm

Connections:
3V3: J1.5, J5.15
BTN_A: J5.2, SW5.1
BTN_B: J5.3, SW6.1
BTN_C: J5.4, SW7.1
BTN_CANCEL: J5.11, SW10.1
BTN_D: J5.5, SW8.1
BTN_DPAD_E: J5.8, SW3.1
BTN_DPAD_N: J5.6, SW1.1
BTN_DPAD_S: J5.7, SW2.1
BTN_DPAD_W: J5.9, SW4.1
BTN_SELECT: J5.10, SW9.1
GND: J1.1, J5.1, J5.P1, J5.P2, SW1.2, SW2.2, SW3.2, SW4.2, SW5.2, SW6.2, SW7.2, SW8.2, SW9.2, SW10.2
I2C_SCL: J1.3, J5.13
I2C_SDA: J1.4, J5.12
TRACKBALL_INTERRUPT: J1.2, J5.14

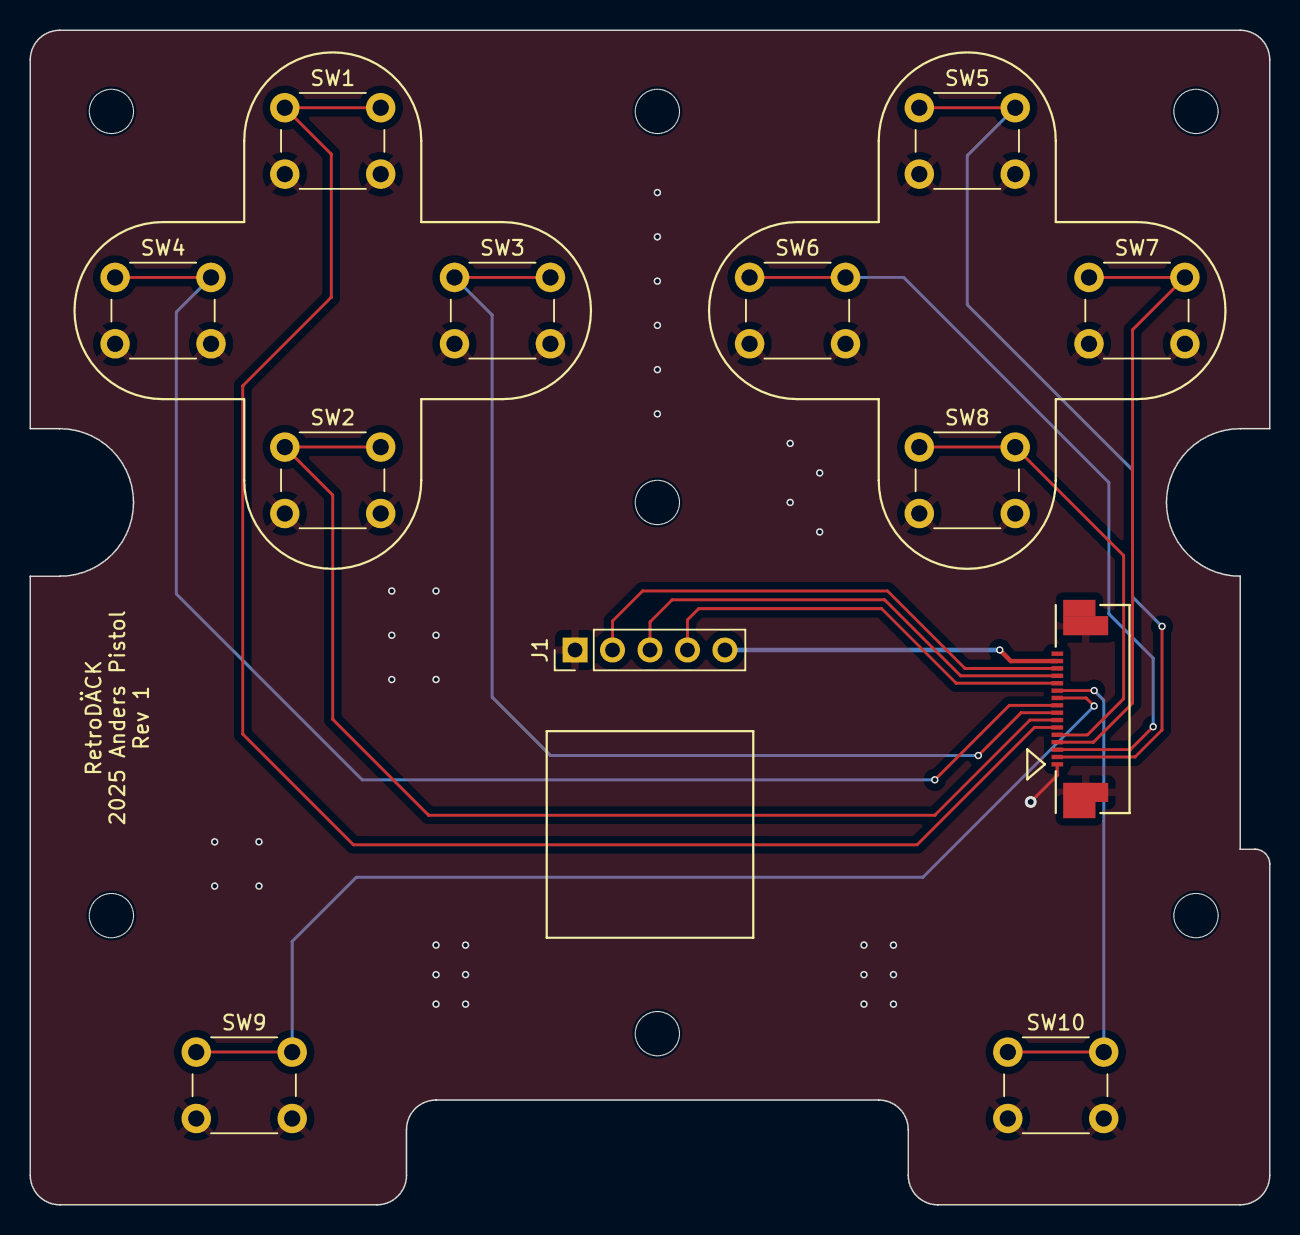
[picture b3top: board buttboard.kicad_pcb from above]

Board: 2 copper layers, 84.0 x 79.6 mm, 19 parts (0 on the bottom side), 15 nets.

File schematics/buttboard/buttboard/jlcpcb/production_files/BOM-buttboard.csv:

Comment,Designator,Footprint,LCSC,Quantity
527461671,J5,CON_527461671_MOL,C3169781,1
Conn_01x05,J1,PinHeader_1x05_P2.54mm_Vertical,,1
D,SW8,SW_PUSH_6mm_H7.3mm,,1
A,SW9,SW_PUSH_6mm_H7.3mm,,1
W,SW4,SW_PUSH_6mm_H7.3mm,,1
A,SW5,SW_PUSH_6mm_H7.3mm,,1
B,SW6,SW_PUSH_6mm_H7.3mm,,1
C,SW7,SW_PUSH_6mm_H7.3mm,,1
B,SW10,SW_PUSH_6mm_H7.3mm,,1
N,SW1,SW_PUSH_6mm_H7.3mm,,1
E,SW3,SW_PUSH_6mm_H7.3mm,,1
S,SW2,SW_PUSH_6mm_H7.3mm,,1

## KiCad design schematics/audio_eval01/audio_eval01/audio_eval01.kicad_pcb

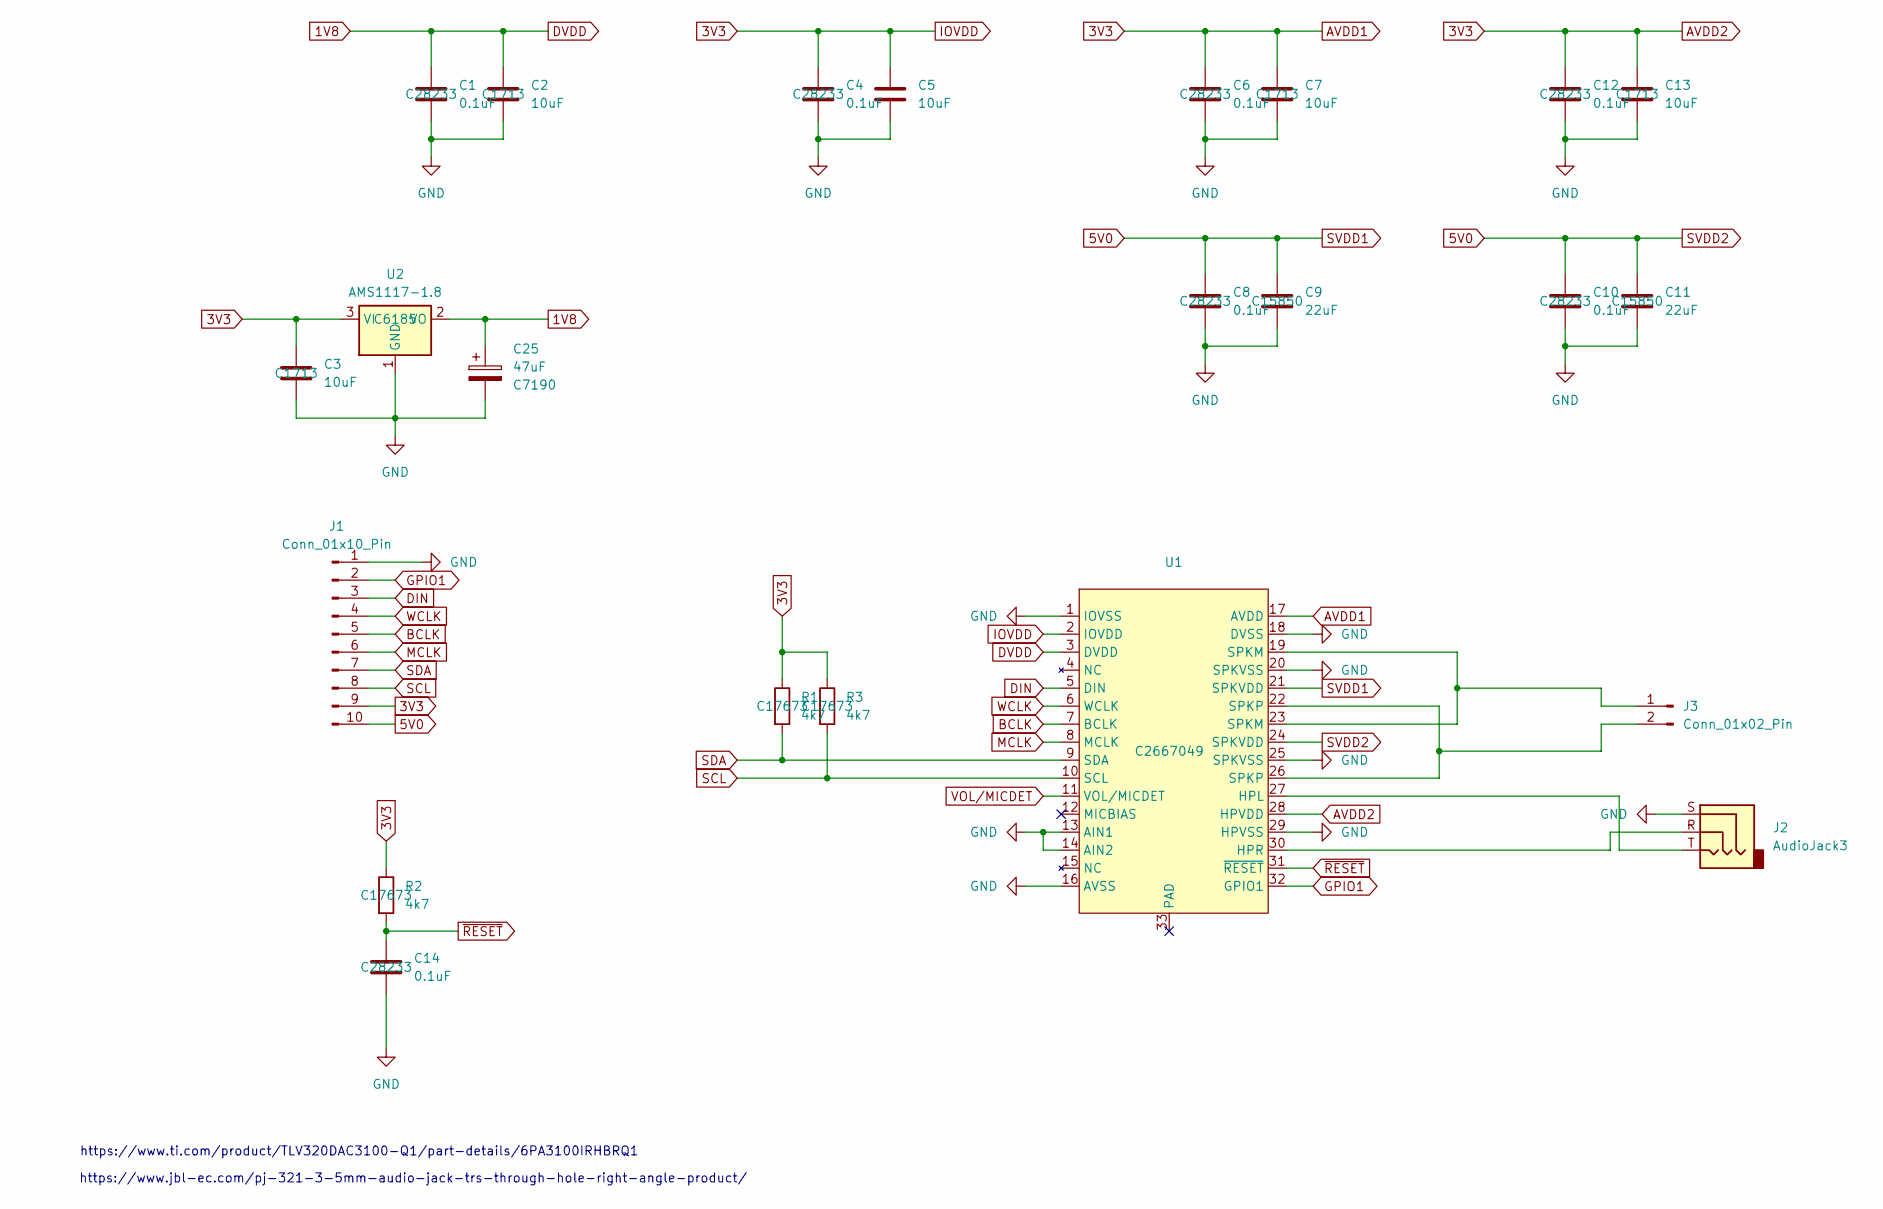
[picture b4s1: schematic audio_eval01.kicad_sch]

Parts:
C1, C4, C6, C8, C10, C12, C14: 0.1uF; C_0805_2012Metric_Pad1.18x1.45mm_HandSolder; LCSC C28233
C2, C3, C5, C7, C13: 10uF; C_0805_2012Metric_Pad1.18x1.45mm_HandSolder; LCSC C1713
C9, C11: 22uF; C_0805_2012Metric_Pad1.18x1.45mm_HandSolder; LCSC C15850
C25: 47uF; CP_EIA-3216-18_Kemet-A; LCSC C7190
J1: Conn_01x10_Pin; PinHeader_1x10_P2.54mm_Vertical
J2: AudioJack3; Jack_3.5mm_Switronic_ST-005-G_horizontal
J3: Conn_01x02_Pin; PinHeader_1x02_P2.54mm_Vertical
R1, R2, R3: 4k7; R_0805_2012Metric_Pad1.20x1.40mm_HandSolder; LCSC C17673
U1: QFN50P500X500X100-33N; LCSC C2667049
U2: AMS1117-1.8; SOT-223-3_TabPin2; LCSC C6185

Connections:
1V8: C1.1, C2.1, C25.1, U1.3 (DVDD), U2.2 (VO)
3V3: C3.1, C4.1, C5.1, C6.1, C7.1, C12.1, C13.1, J1.9, R1.1, R2.1, R3.1, U1.2 (IOVDD), U1.17 (AVDD), U1.28 (HPVDD), U2.3 (VI)
5V0: C8.1, C9.1, C10.1, C11.1, J1.10, U1.21 (SPKVDD), U1.24 (SPKVDD)
BCLK: J1.5, U1.7 (BCLK)
DIN: J1.3, U1.5 (DIN)
GND: C1.2, C2.2, C3.2, C4.2, C5.2, C6.2, C7.2, C8.2, C9.2, C10.2, C11.2, C12.2, C13.2, C14.2, C25.2, J1.1, J2.S, U1.1 (IOVSS), U1.13 (AIN1), U1.14 (AIN2), U1.16 (AVSS), U1.18 (DVSS), U1.20 (SPKVSS), U1.25 (SPKVSS), U1.29 (HPVSS), U2.1 (GND)
GPIO1: J1.2, U1.32 (GPIO1)
MCLK: J1.6, U1.8 (MCLK)
unnamed: J3.1, U1.19 (SPKM), U1.23 (SPKM)
unnamed: J3.2, U1.22 (SPKP), U1.26 (SPKP)
unnamed: J2.T, U1.27 (HPL)
unnamed: J2.R, U1.30 (HPR)
SCL: J1.8, R3.2, U1.10 (SCL)
SDA: J1.7, R1.2, U1.9 (SDA)
VOL/MICDET: U1.11 (VOL/MICDET)
WCLK: J1.4, U1.6 (WCLK)
~RESET: C14.1, R2.2, U1.31 (~RESET)

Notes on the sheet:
https://www.ti.com/product/TLV320DAC3100-Q1/part-details/6PA3100IRHBRQ1
https://www.jbl-ec.com/pj-321-3-5mm-audio-jack-trs-through-hole-right-angle-product/
